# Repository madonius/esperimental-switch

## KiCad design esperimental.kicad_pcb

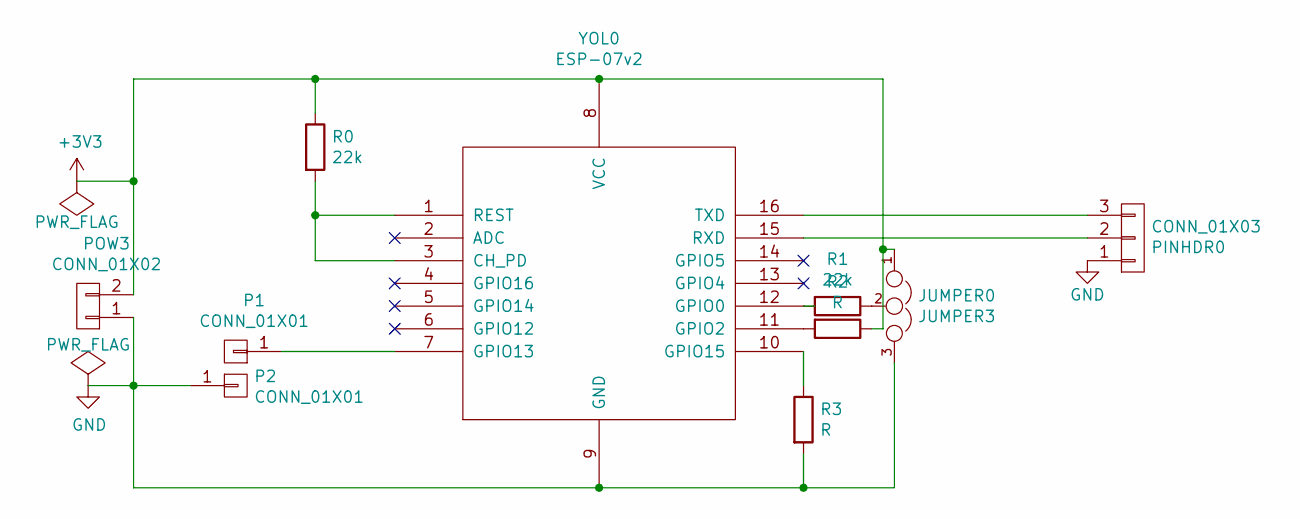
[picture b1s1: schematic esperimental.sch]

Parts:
JUMPER0: JUMPER3; Pin_Header_Straight_1x03
P1, P2: CONN_01X01; Pin_Header_Straight_1x01
PINHDR0: CONN_01X03; Pin_Header_Straight_1x03
POW3: CONN_01X02; Pin_Header_Straight_1x02
R0, R1: 22k; R_0805_HandSoldering
R2, R3: R; R_0805_HandSoldering
YOL0: ESP-07v2; ESP-07v2_smd

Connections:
+3V3: JUMPER0.1, POW3.2, R0.1, R2.1, YOL0.8 (VCC)
GND: JUMPER0.3, P2.1, PINHDR0.1, POW3.1, R3.2, YOL0.9 (GND)
unnamed: JUMPER0.2, R1.1
unnamed: P1.1, YOL0.7 (GPIO13)
unnamed: PINHDR0.2, YOL0.15 (RXD)
unnamed: PINHDR0.3, YOL0.16 (TXD)
unnamed: R0.2, YOL0.1 (REST), YOL0.3 (CH_PD)
unnamed: R1.2, YOL0.12 (GPIO0)
unnamed: R2.2, YOL0.11 (GPIO2)
unnamed: R3.1, YOL0.10 (GPIO15)

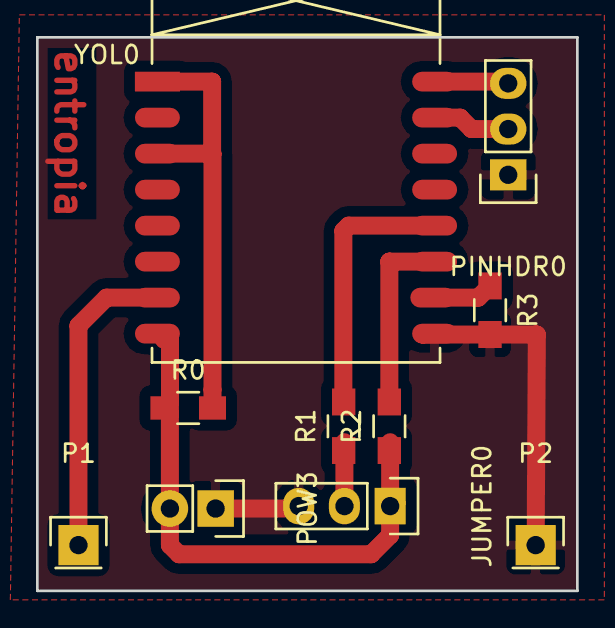
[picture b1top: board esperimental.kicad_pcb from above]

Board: 2 copper layers, 30.0 x 30.8 mm, 10 parts (0 on the bottom side), 10 nets.

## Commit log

2016-06-25 One commit to rule them all
2016-06-25 Renamed the project
2016-06-25 Added a gitignore
2016-06-26 first draft of probably millable board
    * adapt schematic slightly for easier production
    * fix ESP8266 footprint to no longer include unnecessary drill holes
    * add a ground fill
2016-06-27 add entropia text
